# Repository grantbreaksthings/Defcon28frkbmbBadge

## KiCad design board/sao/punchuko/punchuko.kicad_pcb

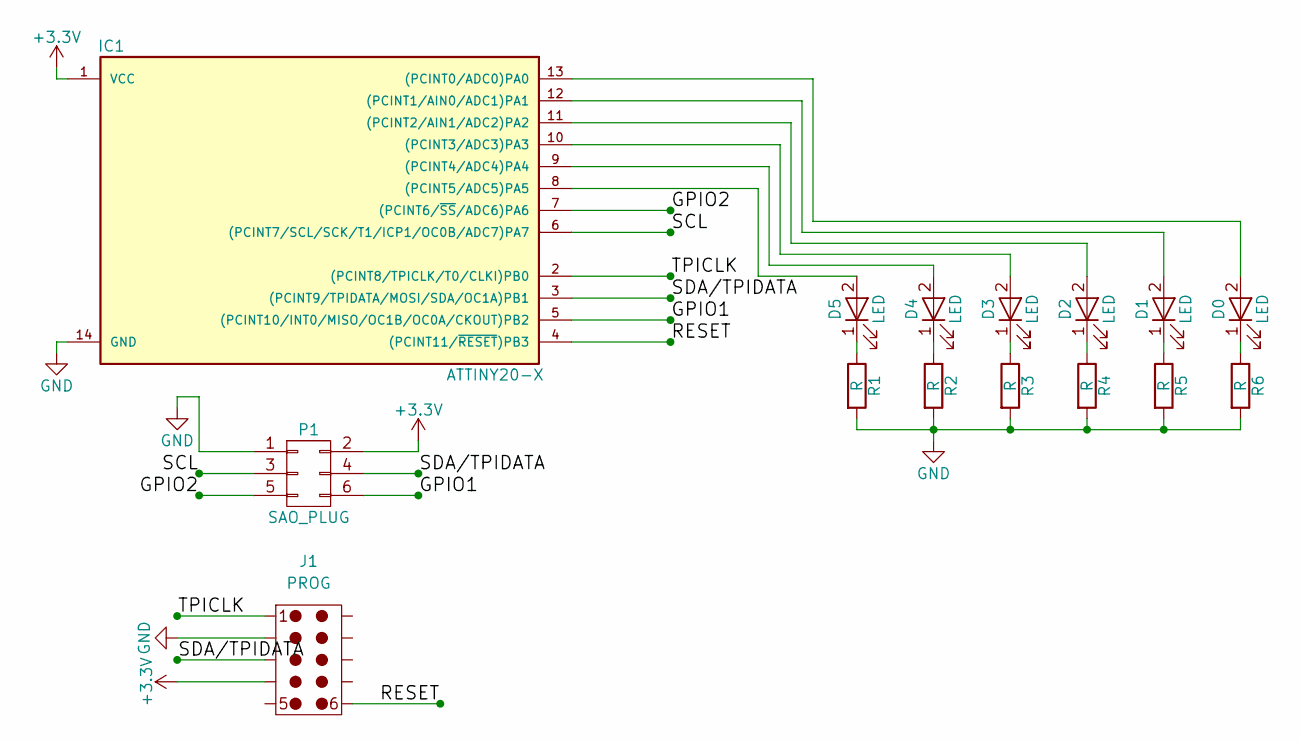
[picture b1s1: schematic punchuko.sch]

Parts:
D0, D1, D2, D3, D4, D5: LED; LED_0603
IC1: ATTINY20-X; ATTINY20_SOIC-14
J1: PROG; TC2050-All_Holes
P1: SAO_PLUG; Socket_Strip_Straight_2x03
R1, R2, R3, R4, R5, R6: R; R_0603_HandSoldering

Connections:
+3V3: IC1.1 (VCC), J1.4, P1.2
/GPIO1: IC1.5 ((PCINT10/INT0/MISO/OC1B/OC0A/CKOUT)PB2), P1.6
/GPIO2: IC1.7 ((PCINT6/~SS~/ADC6)PA6), P1.5
/RESET: IC1.4 ((PCINT11/~RESET~)PB3), J1.6
/SCL: IC1.6 ((PCINT7/SCL/SCK/T1/ICP1/OC0B/ADC7)PA7), P1.3
/SDA/TPIDATA: IC1.3 ((PCINT9/TPIDATA/MOSI/SDA/OC1A)PB1), J1.3, P1.4
/TPICLK: IC1.2 ((PCINT8/TPICLK/T0/CLKI)PB0), J1.1
GND: IC1.14 (GND), J1.2, P1.1, R1.2, R2.2, R3.2, R4.2, R5.2, R6.2
unnamed: D0.1 (K), R6.1
unnamed: D0.2 (A), IC1.13 ((PCINT0/ADC0)PA0)
unnamed: D1.1 (K), R5.1
unnamed: D1.2 (A), IC1.12 ((PCINT1/AIN0/ADC1)PA1)
unnamed: D2.1 (K), R4.1
unnamed: D2.2 (A), IC1.11 ((PCINT2/AIN1/ADC2)PA2)
unnamed: D3.1 (K), R3.1
unnamed: D3.2 (A), IC1.10 ((PCINT3/ADC3)PA3)
unnamed: D4.1 (K), R2.1
unnamed: D4.2 (A), IC1.9 ((PCINT4/ADC4)PA4)
unnamed: D5.1 (K), R1.1
unnamed: D5.2 (A), IC1.8 ((PCINT5/ADC5)PA5)

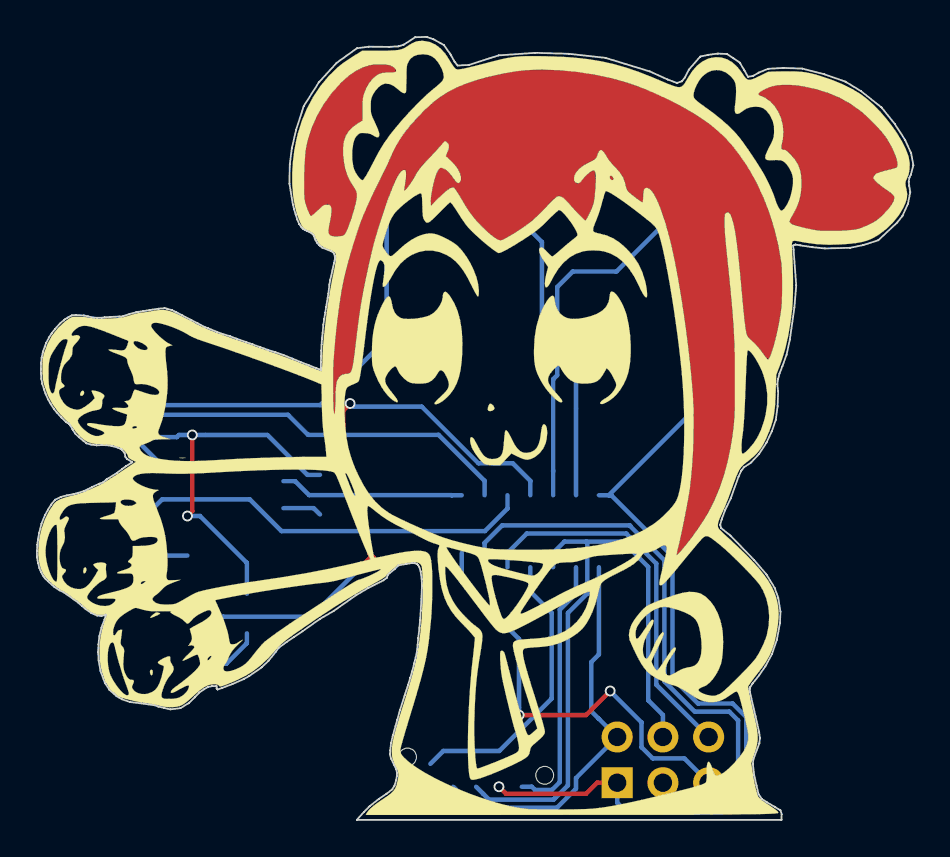
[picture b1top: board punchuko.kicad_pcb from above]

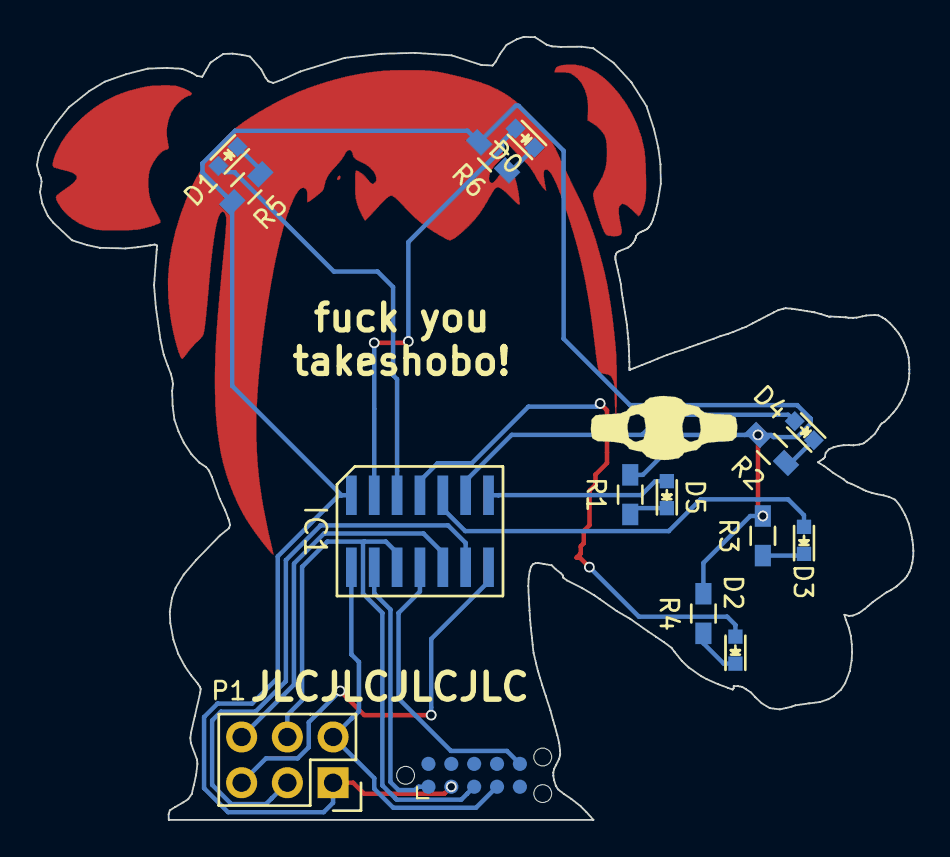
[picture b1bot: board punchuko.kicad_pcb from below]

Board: 2 copper layers, 48.7 x 43.5 mm, 15 parts (15 on the bottom side), 20 nets.

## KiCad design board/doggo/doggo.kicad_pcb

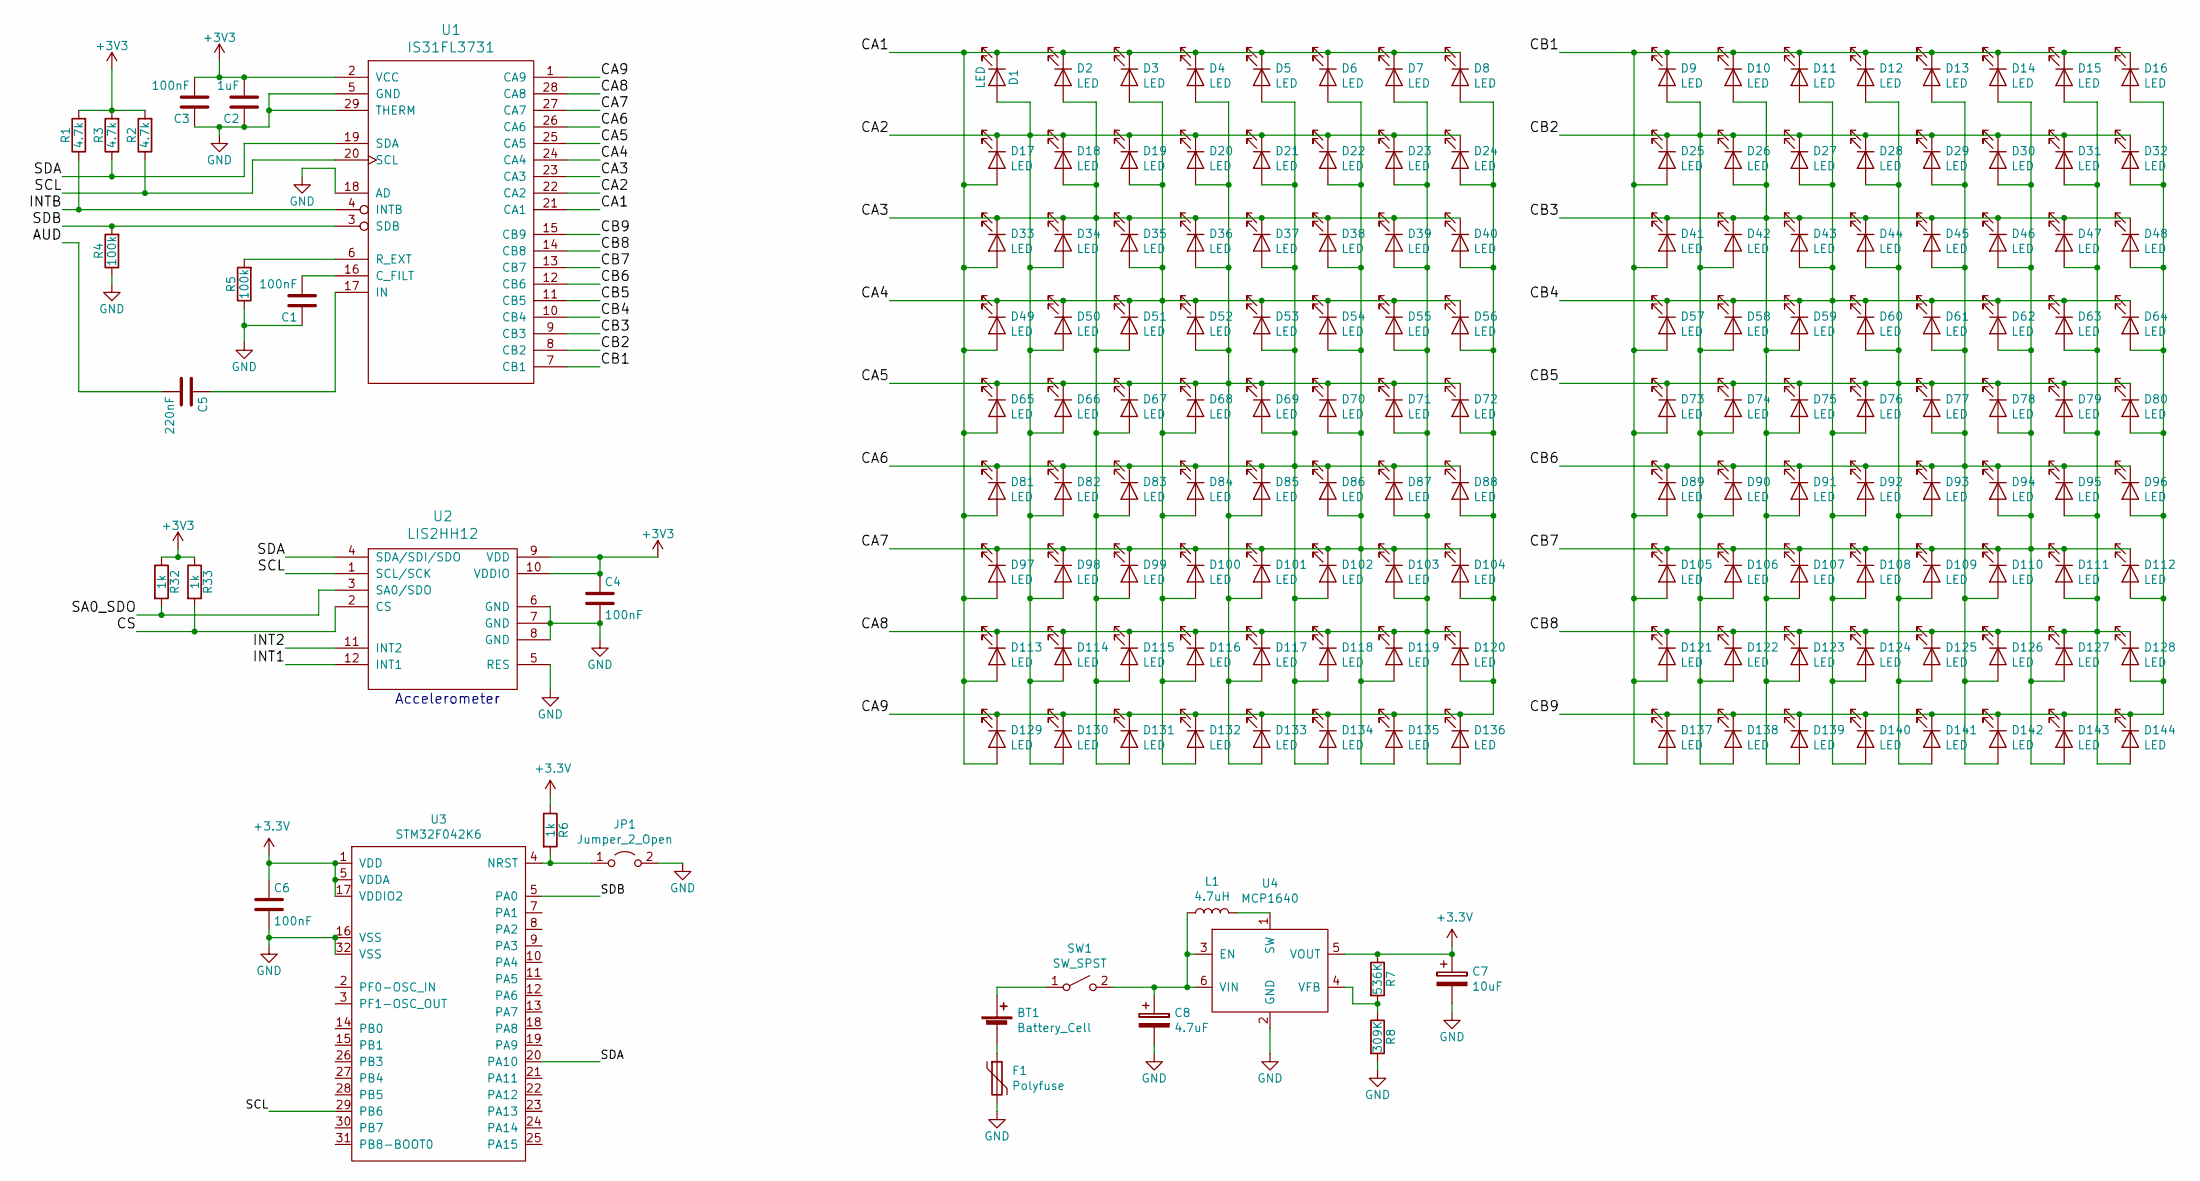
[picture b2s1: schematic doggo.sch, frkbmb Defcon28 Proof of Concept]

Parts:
BT1: Battery_Cell
C1, C3, C4, C6: 100nF; C_0603_1608Metric
C2: 1uF; C_0805_2012Metric
C5: 220nF; C_0603_1608Metric
C7: 10uF; CP_EIA-3216-10_Kemet-I
C8: 4.7uF; CP_EIA-3216-10_Kemet-I
D1, D2, D3, D4, D5, D6, D7, D8, D9, D10, D11, D12, D13, D14, D15, D16, D17, D18, D19, D20, D21, D22, D23, D24, D25, D26, D27, D28, D29, D30, D31, D32, D33, D34, D35, D36, D37, D38, D39, D40, D41, D42, D43, D44, D45, D46, D47, D48, D49, D50, D51, D52, D53, D54, D55, D56, D57, D58, D59, D60, D61, D62, D63, D64, D65, D66, D67, D68, D69, D70, D71, D72, D73, D74, D75, D76, D77, D78, D79, D80, D81, D82, D83, D84, D85, D86, D87, D88, D89, D90, D91, D92, D93, D94, D95, D96, D97, D98, D99, D100, D101, D102, D103, D104, D105, D106, D107, D108, D109, D110, D111, D112, D113, D114, D115, D116, D117, D118, D119, D120, D121, D122, D123, D124, D125, D126, D127, D128, D129, D130, D131, D132, D133, D134, D135, D136, D137, D138, D139, D140, D141, D142, D143, D144: LED; D_0402_1005Metric
F1: Polyfuse; Fuse_1210_3225Metric
JP1: Jumper_2_Open; SolderJumper-2_P1.3mm_Open_TrianglePad1.0x1.5mm
L1: 4.7uH; L_Bourns_SRN6045TA
R1, R2, R3: 4.7k; R_0603_1608Metric
R4, R5: 100k; R_0603_1608Metric
R6, R32, R33: 1k; R_0603_1608Metric
R7: 536K; R_0603_1608Metric
R8: 309K; R_0603_1608Metric
SW1: SW_SPST
U1: IS31FL3731
U2: LIS2HH12
U3: STM32F042K6; LQFP-32_7x7mm_P0.8mm
U4: MCP1640; SOT-23-6

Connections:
/AUD: C5.2
/CA1: D1.1 (K), D2.1 (K), D3.1 (K), D4.1 (K), D5.1 (K), D6.1 (K), D7.1 (K), D8.1 (K), D17.2 (A), D33.2 (A), D49.2 (A), D65.2 (A), D81.2 (A), D97.2 (A), D113.2 (A), D129.2 (A), U1.21 (CA1)
/CA2: D1.2 (A), D17.1 (K), D18.1 (K), D19.1 (K), D20.1 (K), D21.1 (K), D22.1 (K), D23.1 (K), D24.1 (K), D34.2 (A), D50.2 (A), D66.2 (A), D82.2 (A), D98.2 (A), D114.2 (A), D130.2 (A), U1.22 (CA2)
/CA3: D2.2 (A), D18.2 (A), D33.1 (K), D34.1 (K), D35.1 (K), D36.1 (K), D37.1 (K), D38.1 (K), D39.1 (K), D40.1 (K), D51.2 (A), D67.2 (A), D83.2 (A), D99.2 (A), D115.2 (A), D131.2 (A), U1.23 (CA3)
/CA4: D3.2 (A), D19.2 (A), D35.2 (A), D49.1 (K), D50.1 (K), D51.1 (K), D52.1 (K), D53.1 (K), D54.1 (K), D55.1 (K), D56.1 (K), D68.2 (A), D84.2 (A), D100.2 (A), D116.2 (A), D132.2 (A), U1.24 (CA4)
/CA5: D4.2 (A), D20.2 (A), D36.2 (A), D52.2 (A), D65.1 (K), D66.1 (K), D67.1 (K), D68.1 (K), D69.1 (K), D70.1 (K), D71.1 (K), D72.1 (K), D85.2 (A), D101.2 (A), D117.2 (A), D133.2 (A), U1.25 (CA5)
/CA6: D5.2 (A), D21.2 (A), D37.2 (A), D53.2 (A), D69.2 (A), D81.1 (K), D82.1 (K), D83.1 (K), D84.1 (K), D85.1 (K), D86.1 (K), D87.1 (K), D88.1 (K), D102.2 (A), D118.2 (A), D134.2 (A), U1.26 (CA6)
/CA7: D6.2 (A), D22.2 (A), D38.2 (A), D54.2 (A), D70.2 (A), D86.2 (A), D97.1 (K), D98.1 (K), D99.1 (K), D100.1 (K), D101.1 (K), D102.1 (K), D103.1 (K), D104.1 (K), D119.2 (A), D135.2 (A), U1.27 (CA7)
/CA8: D7.2 (A), D23.2 (A), D39.2 (A), D55.2 (A), D71.2 (A), D87.2 (A), D103.2 (A), D113.1 (K), D114.1 (K), D115.1 (K), D116.1 (K), D117.1 (K), D118.1 (K), D119.1 (K), D120.1 (K), D136.2 (A), U1.28 (CA8)
/CA9: D8.2 (A), D24.2 (A), D40.2 (A), D56.2 (A), D72.2 (A), D88.2 (A), D104.2 (A), D120.2 (A), D129.1 (K), D130.1 (K), D131.1 (K), D132.1 (K), D133.1 (K), D134.1 (K), D135.1 (K), D136.1 (K), U1.1 (CA9)
/CB1: D9.1 (K), D10.1 (K), D11.1 (K), D12.1 (K), D13.1 (K), D14.1 (K), D15.1 (K), D16.1 (K), D25.2 (A), D41.2 (A), D57.2 (A), D73.2 (A), D89.2 (A), D105.2 (A), D121.2 (A), D137.2 (A), U1.7 (CB1)
/CB2: D9.2 (A), D25.1 (K), D26.1 (K), D27.1 (K), D28.1 (K), D29.1 (K), D30.1 (K), D31.1 (K), D32.1 (K), D42.2 (A), D58.2 (A), D74.2 (A), D90.2 (A), D106.2 (A), D122.2 (A), D138.2 (A), U1.8 (CB2)
/CB3: D10.2 (A), D26.2 (A), D41.1 (K), D42.1 (K), D43.1 (K), D44.1 (K), D45.1 (K), D46.1 (K), D47.1 (K), D48.1 (K), D59.2 (A), D75.2 (A), D91.2 (A), D107.2 (A), D123.2 (A), D139.2 (A), U1.9 (CB3)
/CB4: D11.2 (A), D27.2 (A), D43.2 (A), D57.1 (K), D58.1 (K), D59.1 (K), D60.1 (K), D61.1 (K), D62.1 (K), D63.1 (K), D64.1 (K), D76.2 (A), D92.2 (A), D108.2 (A), D124.2 (A), D140.2 (A), U1.10 (CB4)
/CB5: D12.2 (A), D28.2 (A), D44.2 (A), D60.2 (A), D73.1 (K), D74.1 (K), D75.1 (K), D76.1 (K), D77.1 (K), D78.1 (K), D79.1 (K), D80.1 (K), D93.2 (A), D109.2 (A), D125.2 (A), D141.2 (A), U1.11 (CB5)
/CB6: D13.2 (A), D29.2 (A), D45.2 (A), D61.2 (A), D77.2 (A), D89.1 (K), D90.1 (K), D91.1 (K), D92.1 (K), D93.1 (K), D94.1 (K), D95.1 (K), D96.1 (K), D110.2 (A), D126.2 (A), D142.2 (A), U1.12 (CB6)
/CB7: D14.2 (A), D30.2 (A), D46.2 (A), D62.2 (A), D78.2 (A), D94.2 (A), D105.1 (K), D106.1 (K), D107.1 (K), D108.1 (K), D109.1 (K), D110.1 (K), D111.1 (K), D112.1 (K), D127.2 (A), D143.2 (A), U1.13 (CB7)
/CB8: D15.2 (A), D31.2 (A), D47.2 (A), D63.2 (A), D79.2 (A), D95.2 (A), D111.2 (A), D121.1 (K), D122.1 (K), D123.1 (K), D124.1 (K), D125.1 (K), D126.1 (K), D127.1 (K), D128.1 (K), D144.2 (A), U1.14 (CB8)
/CB9: D16.2 (A), D32.2 (A), D48.2 (A), D64.2 (A), D80.2 (A), D96.2 (A), D112.2 (A), D128.2 (A), D137.1 (K), D138.1 (K), D139.1 (K), D140.1 (K), D141.1 (K), D142.1 (K), D143.1 (K), D144.1 (K), U1.15 (CB9)
/CS: R33.2, U2.2 (CS)
/INT1: U2.12 (INT1)
/INT2: U2.11 (INT2)
/INTB: R1.1, U1.4 (INTB)
/SA0_SDO: R32.2, U2.3 (SA0/SDO)
/SCL: R2.1, U1.20 (SCL), U2.1 (SCL/SCK), U3.29 (PB6)
/SDA: R3.1, U1.19 (SDA), U2.4 (SDA/SDI/SDO), U3.20 (PA10)
GND: C1.1, C2.1, C3.1, C4.2, C6.2, C7.2, C8.2, F1.2, JP1.2 (B), R4.1, R5.1, R8.2, U1.5 (GND), U1.18 (AD), U1.29 (THERM), U2.5 (RES), U2.6 (GND), U2.7 (GND), U2.8 (GND), U3.16 (VSS), U3.32 (VSS), U4.2 (GND)
unnamed: BT1.1 (+), SW1.1 (A)
unnamed: BT1.2 (-), F1.1
unnamed: C1.2, U1.16 (C_FILT)
unnamed: C5.1, U1.17 (IN)
unnamed: C8.1, L1.1, SW1.2 (B), U4.3 (EN), U4.6 (VIN)
unnamed: JP1.1 (A), R6.2, U3.4 (NRST)
unnamed: L1.2, U4.1 (SW)
unnamed: R5.2, U1.6 (R_EXT)
unnamed: R7.2, R8.1, U4.4 (VFB)

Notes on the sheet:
Accelerometer

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
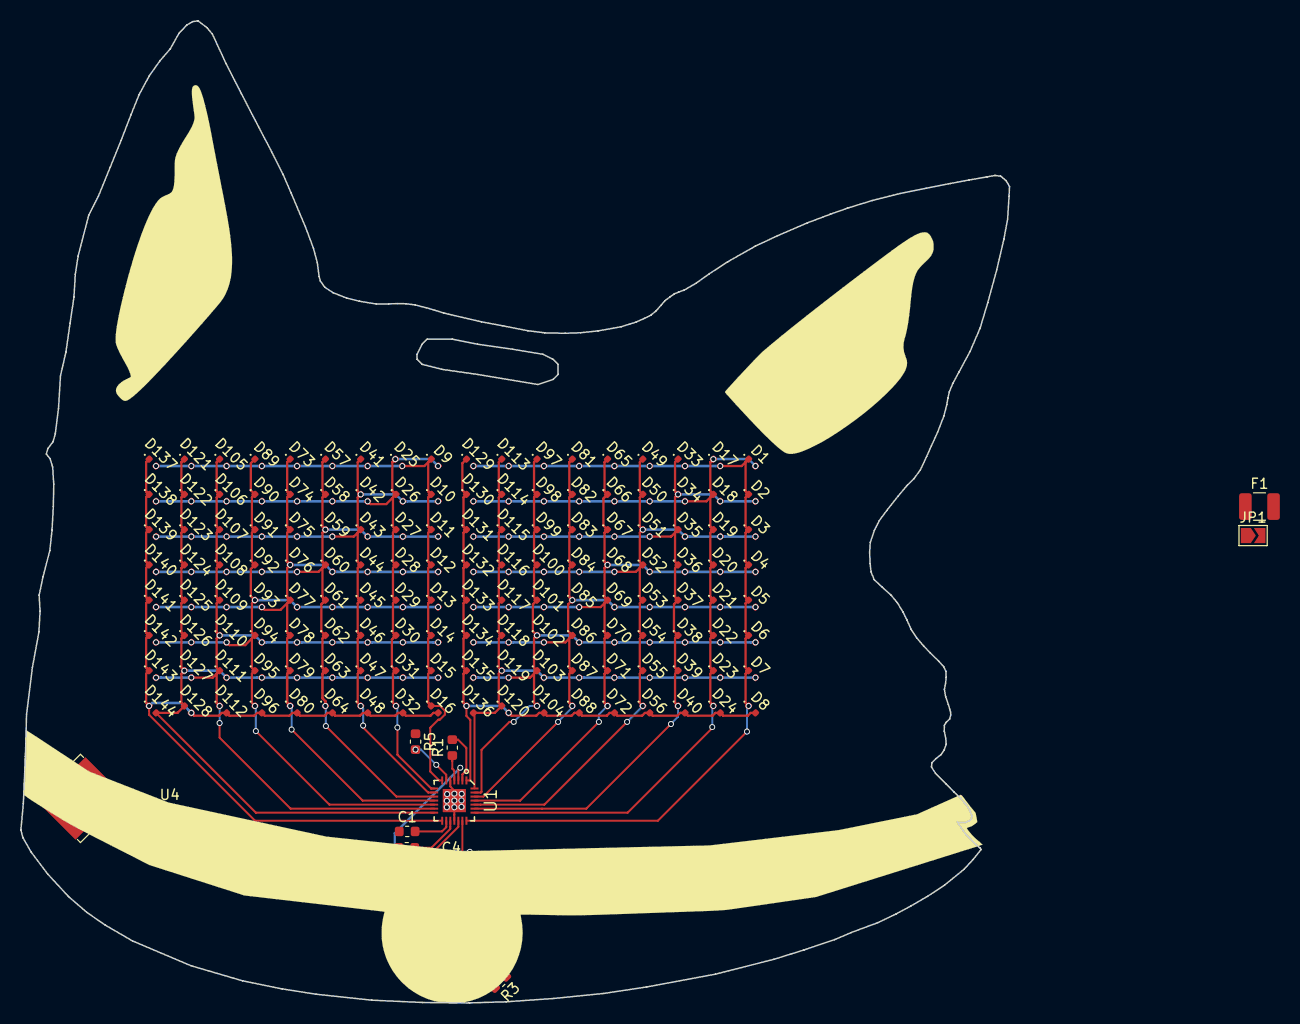
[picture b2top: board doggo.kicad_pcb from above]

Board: 2 copper layers, 98.1 x 97.5 mm, 169 parts (0 on the bottom side), 33 nets.

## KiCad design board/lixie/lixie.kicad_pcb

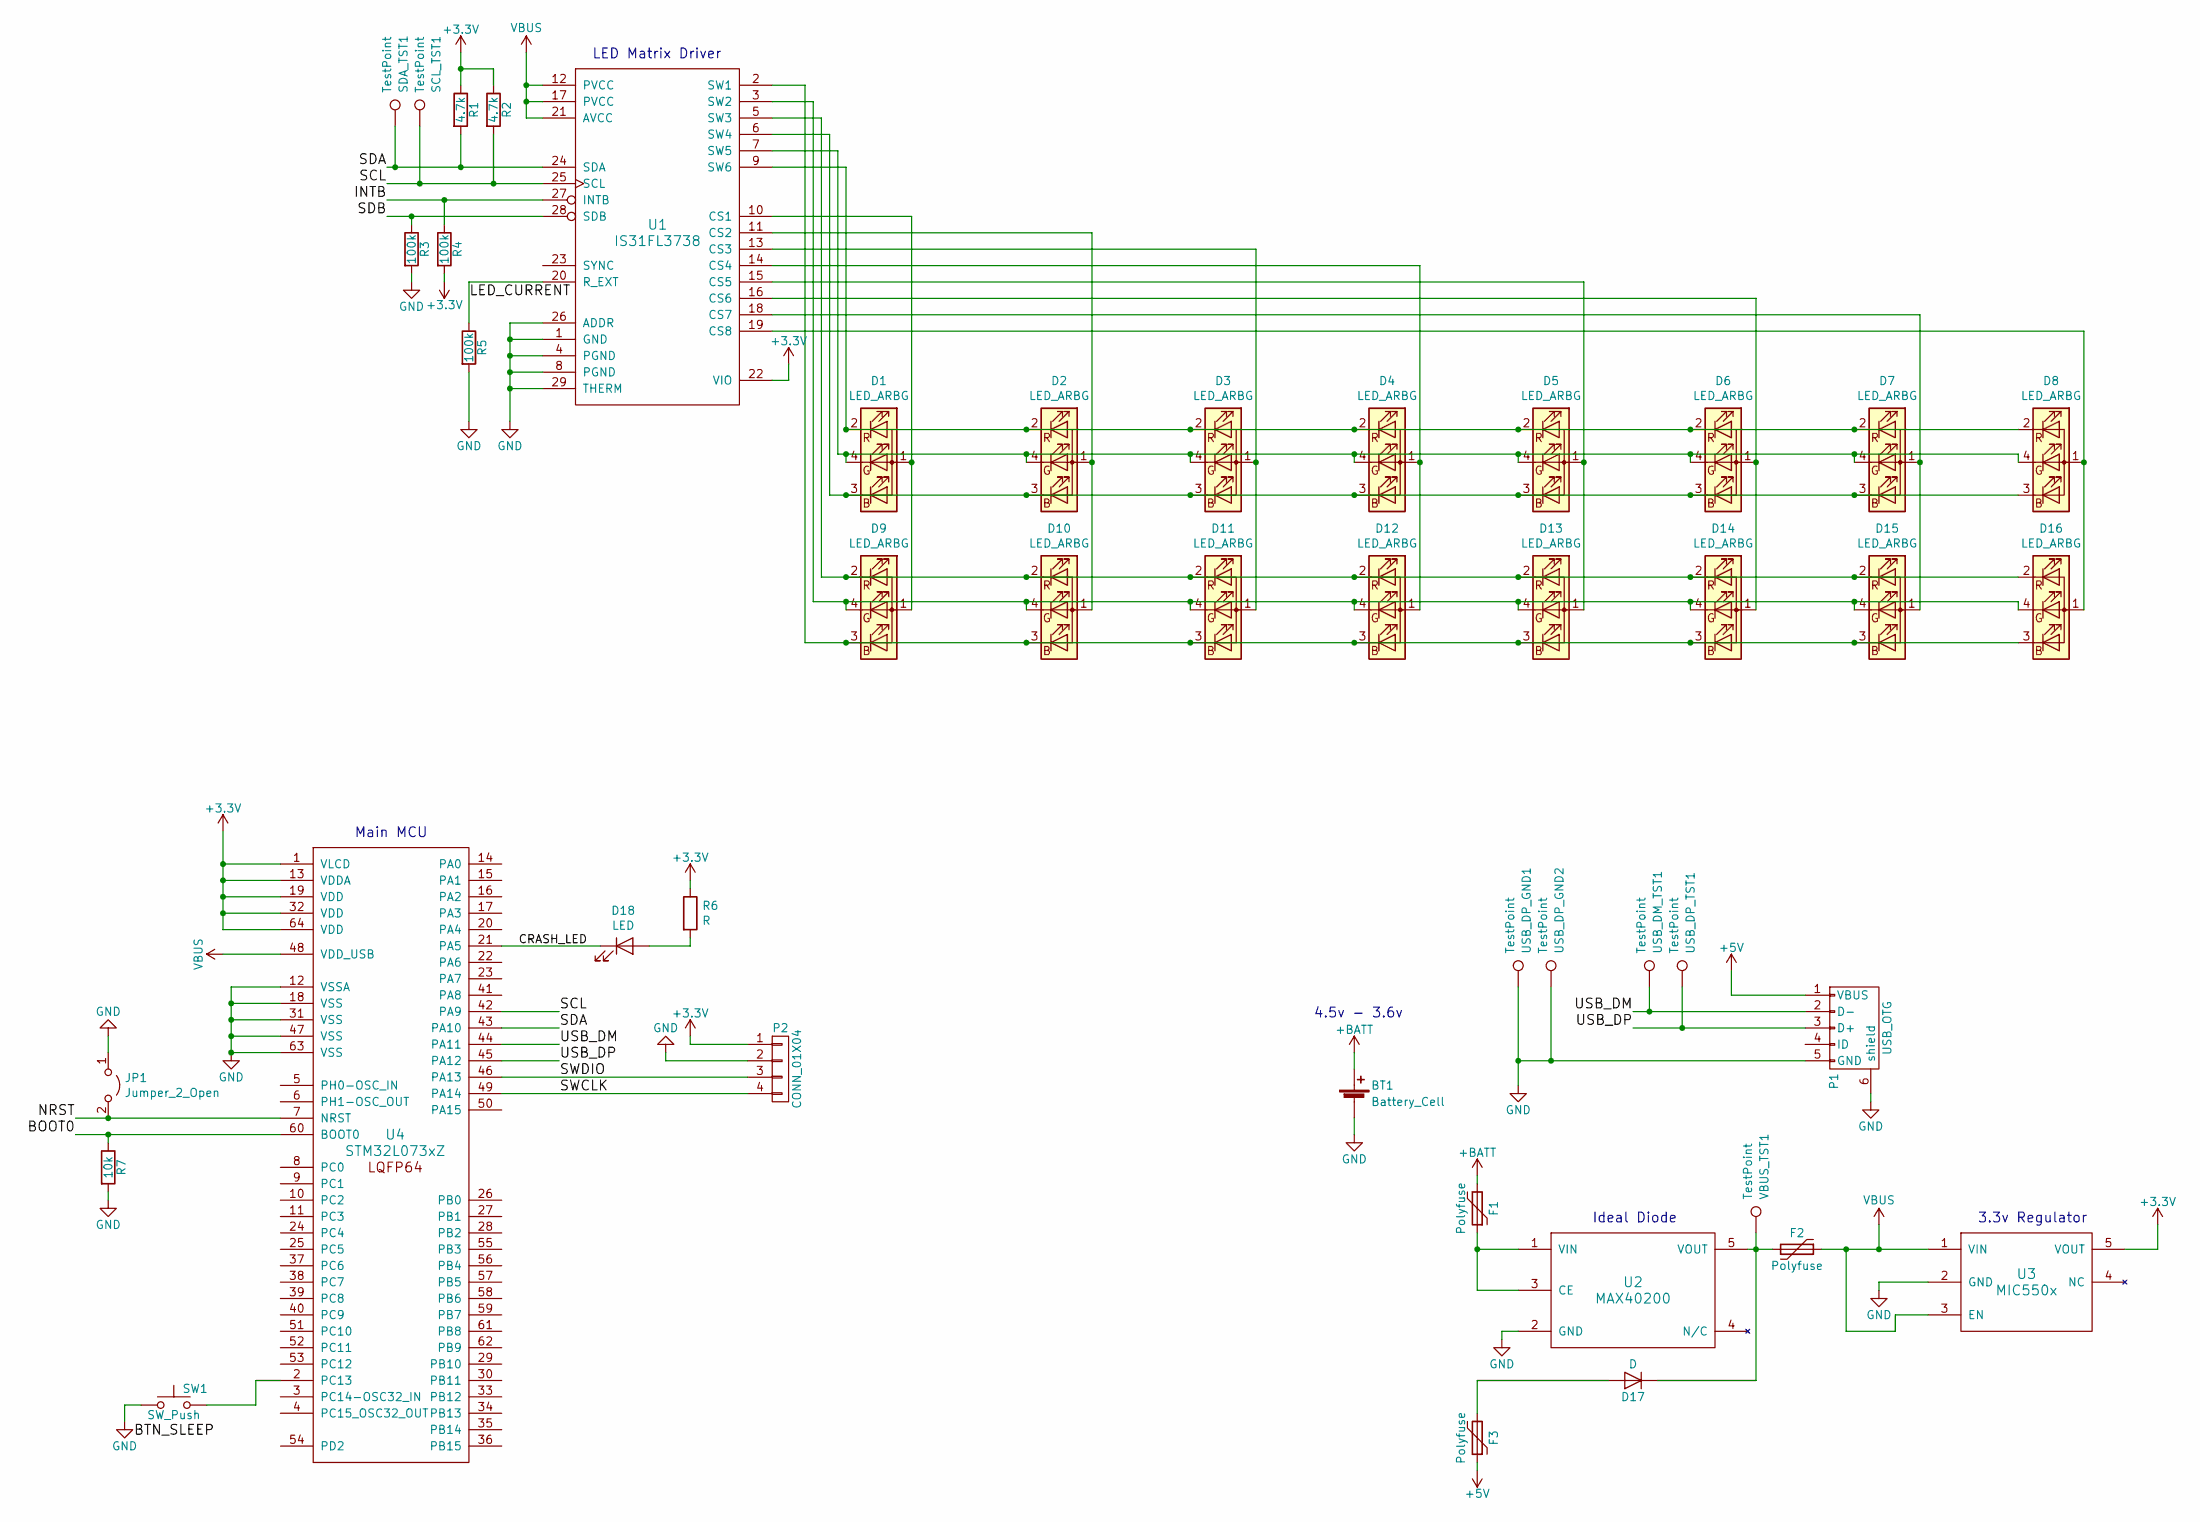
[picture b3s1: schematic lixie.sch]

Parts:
BT1: Battery_Cell; Pin_Header_Straight_1x02
D1, D2, D3, D4, D5, D6, D7, D8, D9, D10, D11, D12, D13, D14, D15, D16: LED_ARBG; LED_LSTD_0606
D17: D; D_SOD-123
D18: LED; LED_0805_2012Metric_Pad1.15x1.40mm_HandSolder
F1, F2, F3: Polyfuse; Fuse_1206_3216Metric_Pad1.42x1.75mm_HandSolder
JP1: Jumper_2_Open; SolderJumper-2_P1.3mm_Open_TrianglePad1.0x1.5mm
P1: USB_OTG; USB_Micro-B_Molex-105017-0001
P2: CONN_01X04; Pin_Header_Straight_1x04
R1, R2: 4.7k; R_0805_2012Metric_Pad1.15x1.40mm_HandSolder
R3, R4, R5: 100k; R_0805_2012Metric_Pad1.15x1.40mm_HandSolder
R6: R; R_0805_2012Metric_Pad1.15x1.40mm_HandSolder
R7: 10k; R_0805_2012Metric_Pad1.15x1.40mm_HandSolder
SCL_TST1: TestPoint; PinHeader_1x01_P2.54mm_Vertical
SDA_TST1: TestPoint; PinHeader_1x01_P2.54mm_Vertical
SW1: SW_Push; SW_SPST_TL3342
U1: IS31FL3738
U2: MAX40200
U3: MIC550x
U4: STM32L073xZ; STM32L073RZT3
USB_DM_TST1: TestPoint; PinHeader_1x01_P2.54mm_Vertical
USB_DP_GND1, USB_DP_GND2: TestPoint; PinHeader_1x01_P2.54mm_Vertical
USB_DP_TST1: TestPoint; PinHeader_1x01_P2.54mm_Vertical
VBUS_TST1: TestPoint; PinHeader_1x01_P2.54mm_Vertical

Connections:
+3V3: P2.1, R1.1, R2.1, R4.2, R6.1, U1.22 (VIO), U3.5 (VOUT), U4.1 (VLCD), U4.13 (VDDA), U4.19 (VDD), U4.32 (VDD), U4.64 (VDD); also elsewhere on the board
+5V: F3.1, P1.1 (VBUS)
+BATT: BT1.1 (+), F1.2
/BOOT0: R7.1, U4.60 (BOOT0)
/CRASH_LED: D18.1 (K), U4.21 (PA5)
/INTB: R4.1, U1.27 (INTB)
/LED_CURRENT: R5.1, U1.20 (R_EXT)
/NRST: JP1.2 (B), U4.7 (NRST)
/SCL: R2.2, SCL_TST1.1, U1.25 (SCL), U4.42 (PA9)
/SDA: R1.2, SDA_TST1.1, U1.24 (SDA), U4.43 (PA10)
/SDB: R3.1, U1.28 (SDB)
/SWCLK: P2.4, U4.49 (PA14); also elsewhere on the board
/SWDIO: P2.3, U4.46 (PA13); also elsewhere on the board
/USB_DM: P1.2 (D-), U4.44 (PA11), USB_DM_TST1.1
/USB_DP: P1.3 (D+), U4.45 (PA12), USB_DP_TST1.1
GND: BT1.2 (-), JP1.1 (A), P1.5 (GND), P1.6 (shield), P2.2, R3.2, R5.2, R7.2, SW1.1, U1.1 (GND), U1.4 (PGND), U1.8 (PGND), U1.26 (ADDR), U1.29 (THERM), U2.2 (GND), U3.2 (GND), U4.12 (VSSA), U4.18 (VSS), U4.31 (VSS), U4.47 (VSS), U4.63 (VSS), USB_DP_GND1.1, USB_DP_GND2.1; also elsewhere on the board
unnamed: D1.1 (A), D9.1 (A), U1.10 (CS1)
unnamed: D1.2 (RK), D2.2 (RK), D3.2 (RK), D4.2 (RK), D5.2 (RK), D6.2 (RK), D7.2 (RK), D8.2 (RK), U1.9 (SW6)
unnamed: D1.3 (BK), D2.3 (BK), D3.3 (BK), D4.3 (BK), D5.3 (BK), D6.3 (BK), D7.3 (BK), D8.3 (BK), U1.6 (SW4)
unnamed: D1.4 (GK), D2.4 (GK), D3.4 (GK), D4.4 (GK), D5.4 (GK), D6.4 (GK), D7.4 (GK), D8.4 (GK), U1.7 (SW5)
unnamed: D2.1 (A), D10.1 (A), U1.11 (CS2)
unnamed: D9.2 (RK), D10.2 (RK), D11.2 (RK), D12.2 (RK), D13.2 (RK), D14.2 (RK), D15.2 (RK), D16.2 (RK), U1.5 (SW3)
unnamed: D9.3 (BK), D10.3 (BK), D11.3 (BK), D12.3 (BK), D13.3 (BK), D14.3 (BK), D15.3 (BK), D16.3 (BK), U1.2 (SW1)
unnamed: D9.4 (GK), D10.4 (GK), D11.4 (GK), D12.4 (GK), D13.4 (GK), D14.4 (GK), D15.4 (GK), D16.4 (GK), U1.3 (SW2)
unnamed: D3.1 (A), D11.1 (A), U1.13 (CS3)
unnamed: D4.1 (A), D12.1 (A), U1.14 (CS4)
unnamed: D5.1 (A), D13.1 (A), U1.15 (CS5)
unnamed: D6.1 (A), D14.1 (A), U1.16 (CS6)
unnamed: D7.1 (A), D15.1 (A), U1.18 (CS7)
unnamed: D8.1 (A), D16.1 (A), U1.19 (CS8)
unnamed: D17.1 (K), F2.2, U2.5 (VOUT), VBUS_TST1.1
unnamed: D17.2 (A), F3.2
unnamed: D18.2 (A), R6.2
unnamed: F1.1, U2.1 (VIN), U2.3 (CE)
unnamed 35: SW1.2, U4.2 (PC13); also elsewhere on the board
VBUS: F2.1, U1.12 (PVCC), U1.17 (PVCC), U1.21 (AVCC), U3.1 (VIN), U3.3 (EN), U4.48 (VDD_USB)

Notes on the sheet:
4.5v - 3.6v
Ideal Diode
3.3v Regulator
LED Matrix Driver
Main MCU

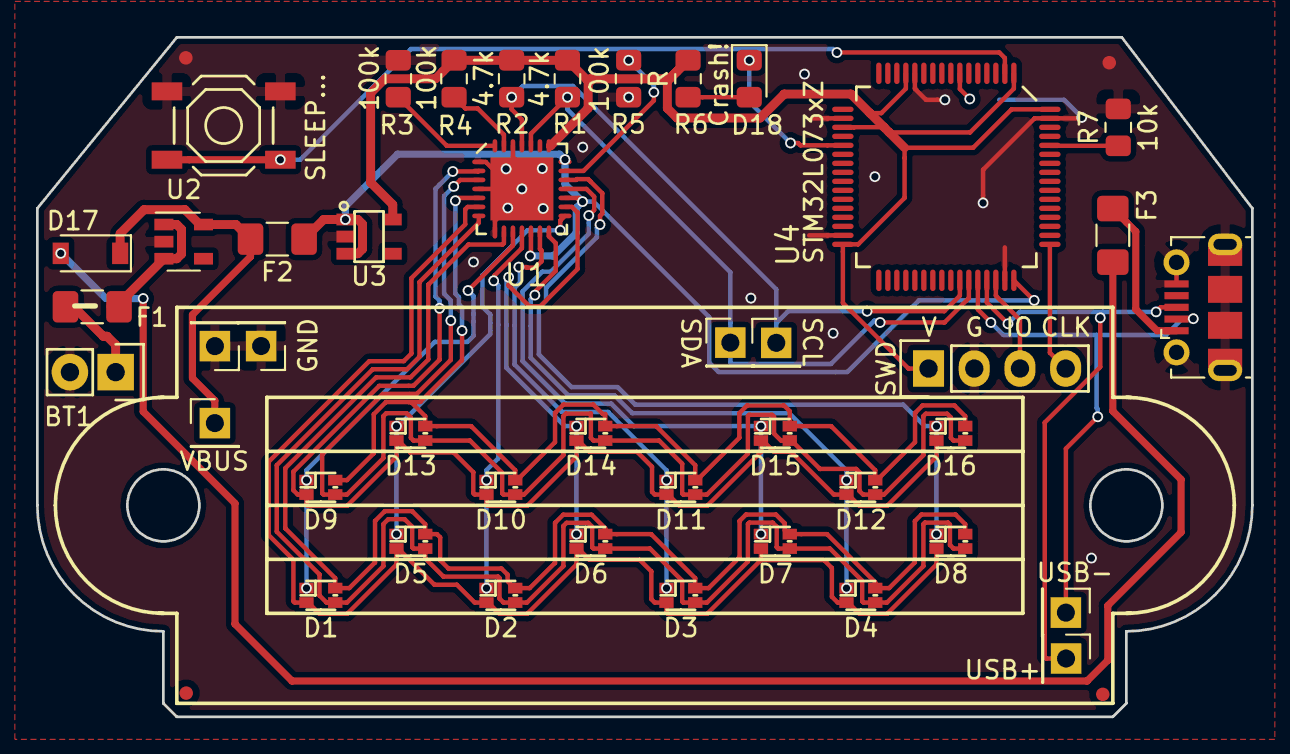
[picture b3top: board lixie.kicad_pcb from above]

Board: 2 copper layers, 67.5 x 37.8 mm, 44 parts (1 on the bottom side), 36 nets.

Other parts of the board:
SLEEP...: SW_Push; SW_SPST_TL3342
SWD: CONN_01X04; Pin_Header_Straight_1x04

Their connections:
+3V3: SWD.1; also elsewhere on the board
/SWCLK: SWD.4; also elsewhere on the board
/SWDIO: SWD.3; also elsewhere on the board
GND: SLEEP....1, SWD.2; also elsewhere on the board
unnamed 35: SLEEP....2; also elsewhere on the board

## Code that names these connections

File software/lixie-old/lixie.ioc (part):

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Mcu.Name=STM32L073R(B-Z)Tx
Mcu.Package=LQFP64
Mcu.UserName=STM32L073RZTx
PA10.Mode=I2C
PA10.Signal=I2C1_SDA
PA11.Mode=Device
PA11.Signal=USB_DM
PA12.Mode=Device
PA12.Signal=USB_DP
PA13.GPIOParameters=GPIO_Label
PA13.GPIO_Label=TMS
PA13.Mode=Serial_Wire
PA13.Signal=SYS_SWDIO
PA14.GPIOParameters=GPIO_Label
PA14.GPIO_Label=TCK
PA14.Mode=Serial_Wire
PA14.Signal=SYS_SWCLK
PA5.GPIOParameters=GPIO_Label
PA5.GPIO_Label=LD2 [Green Led]
PA5.Signal=GPIO_Output
PA9.Mode=I2C
PA9.Signal=I2C1_SCL
PC13.GPIOParameters=GPIO_Label,GPIO_ModeDefaultEXTI
PC13.GPIO_Label=B1 [Blue PushButton]
PC13.GPIO_ModeDefaultEXTI=GPIO_MODE_IT_FALLING
PC13.Signal=GPXTI13
RCC.HSE_VALUE=8000000
RCC.SYSCLKFreq_VALUE=16000000
RCC.SYSCLKSource=RCC_SYSCLKSOURCE_HSI
board=NUCLEO-L073RZ
boardIOC=true

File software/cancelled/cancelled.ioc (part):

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Mcu.Name=STM32F042K(4-6)Tx
Mcu.Package=LQFP32
Mcu.UserName=STM32F042K6Tx
PA0.Signal=GPIO_Output
PA10.Mode=I2C
PA10.Signal=I2C1_SDA
PA13.GPIOParameters=GPIO_Label
PA13.GPIO_Label=SWDIO
PA13.Mode=Serial_Wire
PA13.Signal=SYS_SWDIO
PA14.GPIOParameters=GPIO_Label
PA14.GPIO_Label=SWCLK
PA14.Mode=Serial_Wire
PA14.Signal=SYS_SWCLK
PA15.GPIOParameters=GPIO_Label
PA15.GPIO_Label=VCP_RX
PA15.Signal=USART2_RX
PA2.GPIOParameters=GPIO_Label
PA2.GPIO_Label=VCP_TX
PA2.Signal=USART2_TX
PB6.Mode=I2C
PB6.Signal=I2C1_SCL
PF0-OSC_IN.GPIOParameters=GPIO_Label
PF0-OSC_IN.GPIO_Label=MCO
PF0-OSC_IN.Mode=HSE-External-Clock-Source
PF0-OSC_IN.Signal=RCC_OSC_IN
board=NUCLEO-F042K6
boardIOC=true
